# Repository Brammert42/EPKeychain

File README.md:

# DisplayKeychain
This repository is used to track FW development for Display Keychain using a RP2040 and waveshare Display.

# Manual
## Next image  
Holding the middle button for 4 seconds changes the image on the display to next image in the list.

## Previous image
Holding the middle button and the left button (button closet to the small hole) for 4 seconds changes the image on the display to previous image in the list.

## Uploading new FW  
Get the FW files here:   https://github.com/Brammert42/EPKeychain/tree/main/FW%20version
1: insert push pin in the hole next to the "previous" button untill you feel a "click"  
2: while the push pin is inserted insert the micro USB.  
3: on your PC the keychain will show up as flash drive as RPI-RP2, drag the new FW file into this

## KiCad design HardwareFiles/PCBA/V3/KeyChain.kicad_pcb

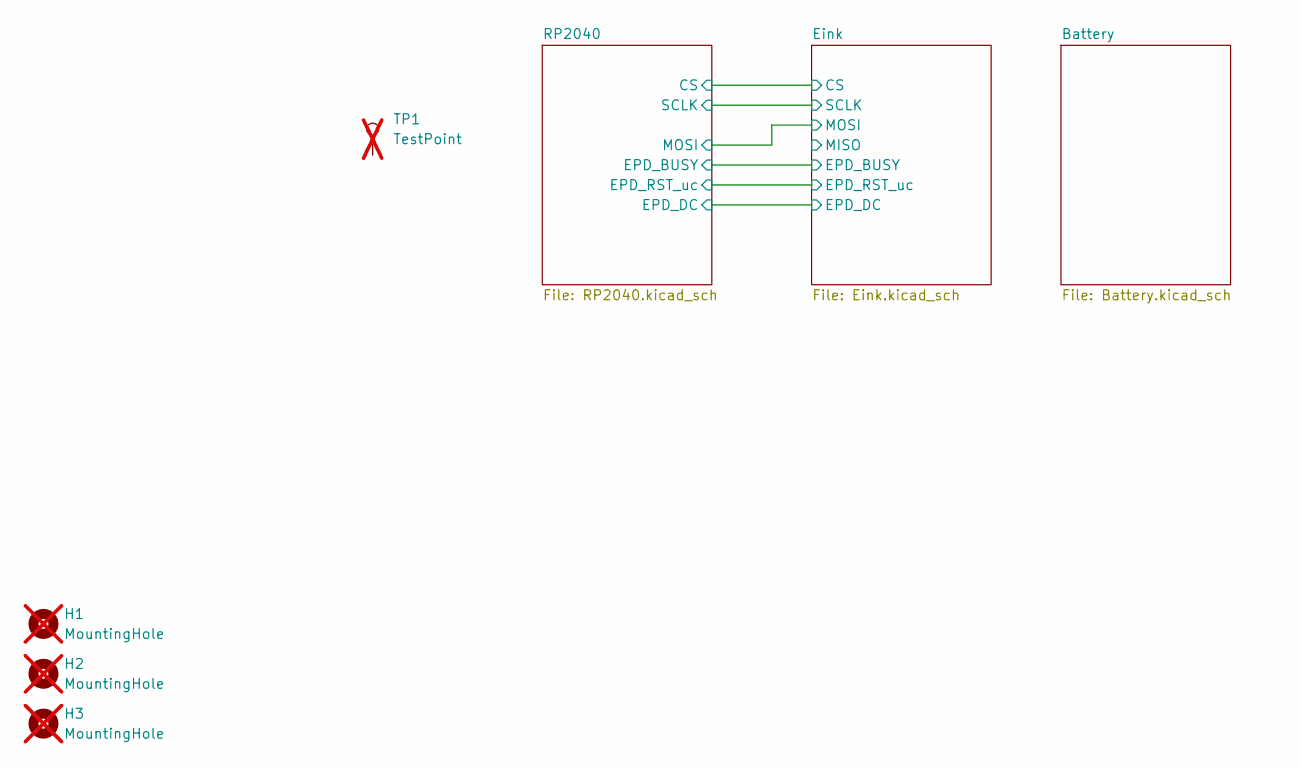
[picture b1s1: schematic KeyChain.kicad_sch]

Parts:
H1, H2, H3: MountingHole; MountingHole_2.1mm; not fitted
TP1: TestPoint; display; MPN dnf; not fitted

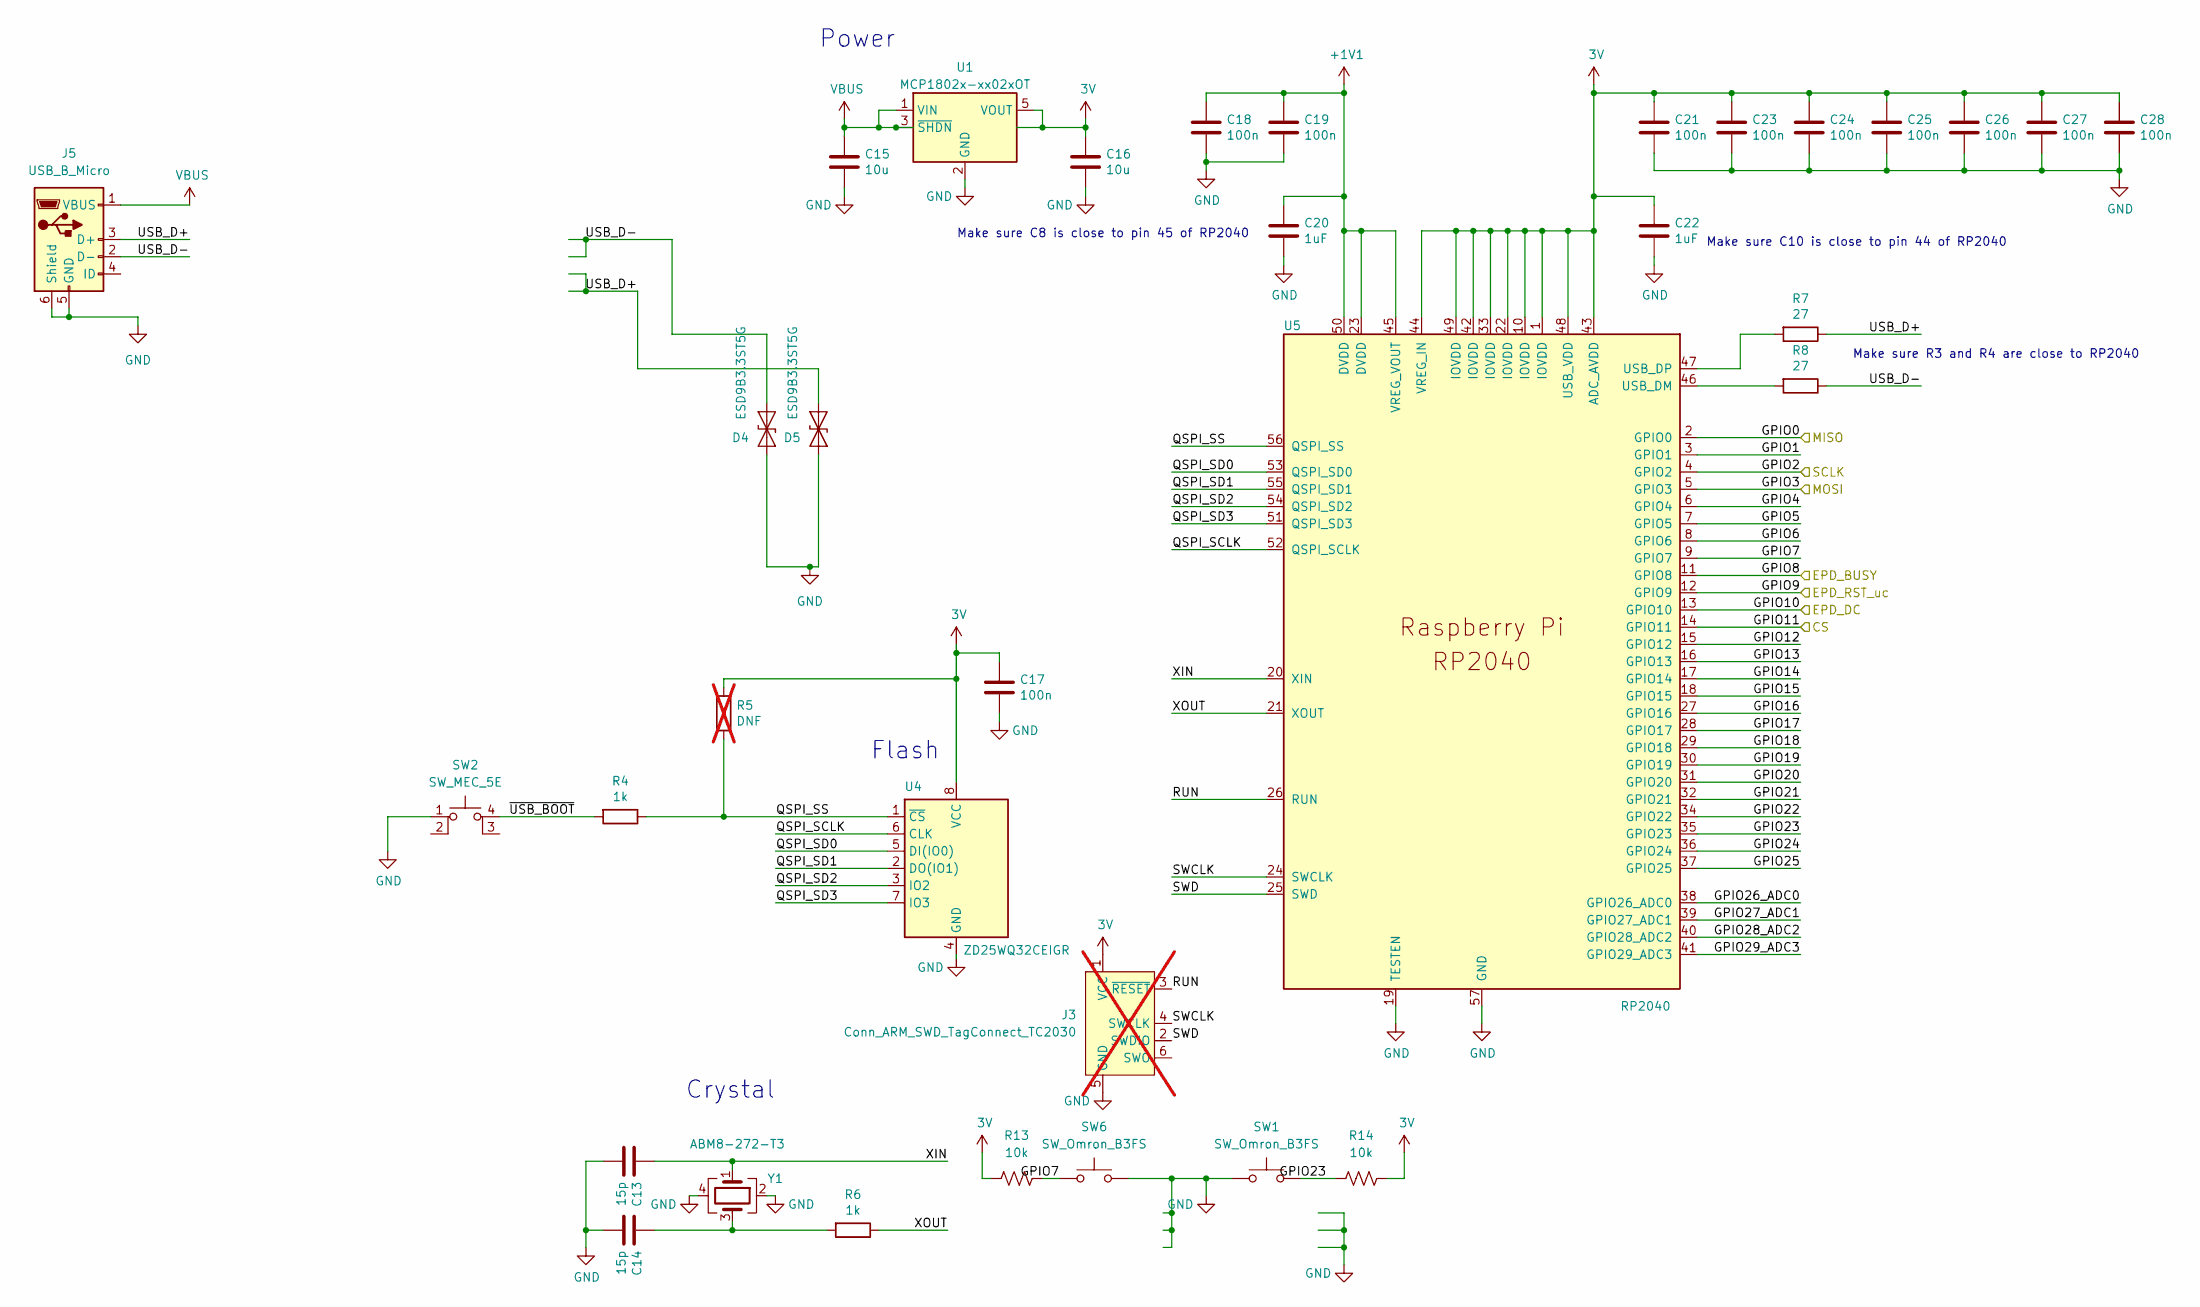
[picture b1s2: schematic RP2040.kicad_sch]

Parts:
C13, C14: 15p; C_0402_1005Metric; MPN C1548
C15, C16: 10u; C_0402_1005Metric; MPN C23733
C17, C18, C19, C21, C23, C24, C25, C26, C27, C28: 100n; C_0402_1005Metric; MPN C307331
C20, C22: 1uF; C_0402_1005Metric; MPN C52923
D4, D5: ESD9B3.3ST5G; D_SOD-923; MPN C3021104
J3: Conn_ARM_SWD_TagConnect_TC2030; Tag-Connect_TC2030-IDC-NL_2x03_P1.27mm_Vertical; not fitted
J5: USB_B_Micro; USB_Micro-B_Wuerth_614105150721_Vertical; MPN C668588
R4, R6: 1k; R_0402_1005Metric; MPN C11702
R5: DNF; R_0402_1005Metric; MPN dnf; not fitted
R7, R8: 27; R_0402_1005Metric; MPN C25100
R13, R14: 10k; R_0402_1005Metric; MPN C25744
SW1, SW6: SW_Omron_B3FS; SW_SPST_Omron_B3FS-100xP; MPN C5127964
SW2: SW_MEC_5E; SW_SPST_TL3342; MPN C318884
U1: MCP1802x-xx02xOT; SOT-23-5; MPN C7419952
U4: ZD25WQ32CEIGR; SON50P300X200X60-9N; MPN C5258281
U5: RP2040; QFN-56-1EP_7x7mm_P0.4mm_EP3.2x3.2mm; MPN C2040
Y1: ABM8-272-T3; Crystal_SMD_3225-4Pin_3.2x2.5mm; MPN C9002

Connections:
3V: C16.1, C17.1, C21.1, C22.1, C23.1, C24.1, C25.1, C26.1, C27.1, C28.1, J3.1 (VCC), R5.1, R13.1, R14.2, U1.4 (NC), U1.5 (VOUT), U4.8 (VCC), U5.1 (IOVDD), U5.10 (IOVDD), U5.22 (IOVDD), U5.33 (IOVDD), U5.42 (IOVDD), U5.43 (ADC_AVDD), U5.44 (VREG_IN), U5.48 (USB_VDD), U5.49 (IOVDD); also elsewhere on the board
+1V1: C18.1, C19.1, C20.1, U5.23 (DVDD), U5.45 (VREG_VOUT), U5.50 (DVDD)
/Eink/CLK: U5.4 (GPIO2); also elsewhere on the board
/Eink/DIN: U5.5 (GPIO3); also elsewhere on the board
/Eink/EPD_BUSY: U5.11 (GPIO8); also elsewhere on the board
/Eink/EPD_CS: U5.14 (GPIO11); also elsewhere on the board
/Eink/EPD_DC: U5.13 (GPIO10); also elsewhere on the board
/Eink/EPD_RST: U5.12 (GPIO9); also elsewhere on the board
/RP2040/GPIO0: U5.2 (GPIO0)
/RP2040/GPIO1: U5.3 (GPIO1)
/RP2040/GPIO4: U5.6 (GPIO4)
/RP2040/GPIO5: U5.7 (GPIO5)
/RP2040/GPIO6: U5.8 (GPIO6)
/RP2040/GPIO7: R13.2, SW6.1, U5.9 (GPIO7)
/RP2040/GPIO12: U5.15 (GPIO12)
/RP2040/GPIO13: U5.16 (GPIO13)
/RP2040/GPIO14: U5.17 (GPIO14)
/RP2040/GPIO15: U5.18 (GPIO15)
/RP2040/GPIO16: U5.27 (GPIO16)
/RP2040/GPIO17: U5.28 (GPIO17)
/RP2040/GPIO18: U5.29 (GPIO18)
/RP2040/GPIO19: U5.30 (GPIO19)
/RP2040/GPIO20: U5.31 (GPIO20)
/RP2040/GPIO21: U5.32 (GPIO21)
/RP2040/GPIO22: U5.34 (GPIO22)
/RP2040/GPIO23: R14.1, SW1.2, U5.35 (GPIO23)
/RP2040/GPIO24: U5.36 (GPIO24)
/RP2040/GPIO25: U5.37 (GPIO25)
/RP2040/GPIO26_ADC0: U5.38 (GPIO26_ADC0)
/RP2040/GPIO27_ADC1: U5.39 (GPIO27_ADC1)
/RP2040/GPIO28_ADC2: U5.40 (GPIO28_ADC2)
/RP2040/GPIO29_ADC3: U5.41 (GPIO29_ADC3)
/RP2040/QSPI_SCLK: U4.6 (CLK), U5.52 (QSPI_SCLK)
/RP2040/QSPI_SD0: U4.5 (DI(IO0)), U5.53 (QSPI_SD0)
/RP2040/QSPI_SD1: U4.2 (DO(IO1)), U5.55 (QSPI_SD1)
/RP2040/QSPI_SD2: U4.3 (IO2), U5.54 (QSPI_SD2)
/RP2040/QSPI_SD3: U4.7 (IO3), U5.51 (QSPI_SD3)
/RP2040/QSPI_SS: R4.1, R5.2, U4.1 (~CS), U5.56 (QSPI_SS)
/RP2040/RUN: J3.3 (~RESET), U5.26 (RUN)
/RP2040/SWCLK: J3.4 (SWCLK), U5.24 (SWCLK)
/RP2040/SWD: J3.2 (SWDIO), U5.25 (SWD)
/RP2040/USB_D+: D5.1 (A1), J5.3 (D+), R7.1
/RP2040/USB_D-: D4.1 (A1), J5.2 (D-), R8.1
/RP2040/XIN: C13.1, U5.20 (XIN), Y1.1
/RP2040/XOUT: R6.1, U5.21 (XOUT)
/RP2040/~USB_BOOT: R4.2, SW2.4 (A)
GND: C13.2, C14.2, C15.2, C16.2, C17.2, C18.2, C19.2, C20.2, C21.2, C22.2, C23.2, C24.2, C25.2, C26.2, C27.2, C28.2, D4.2 (A2), D5.2 (A2), J3.5 (GND), J5.5 (GND), J5.6 (Shield), SW1.1, SW2.1, SW6.2, U1.2 (GND), U4.4 (GND), U5.19 (TESTEN), U5.57 (GND), Y1.2, Y1.4; also elsewhere on the board
unnamed: C14.1, R6.2, Y1.3
unnamed: R8.2, U5.46 (USB_DM)
unnamed: R7.2, U5.47 (USB_DP)
VBUS: C15.1, J5.1 (VBUS), U1.1 (VIN), U1.3 (~SHDN)

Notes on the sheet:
Make sure R3 and R4 are close to RP2040
Power
Crystal
Make sure C10 is close to pin 44 of RP2040
Flash
Make sure C8 is close to pin 45 of RP2040

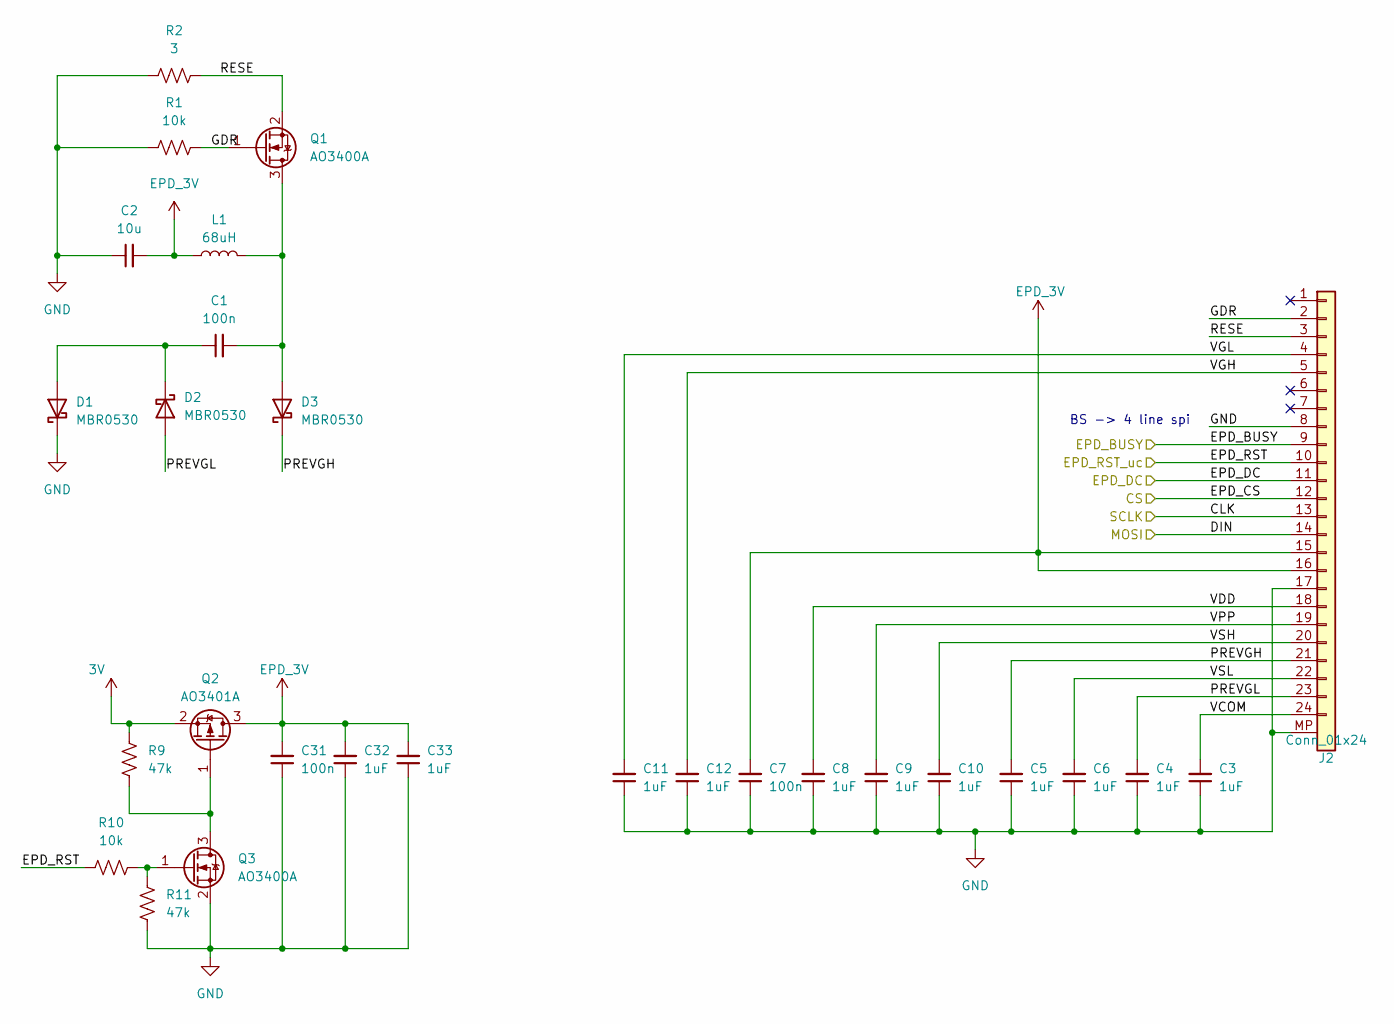
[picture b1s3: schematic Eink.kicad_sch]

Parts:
C1, C7, C31: 100n; C_0402_1005Metric; MPN C307331
C2: 10u; C_0402_1005Metric; MPN C23733
C3, C4, C5, C6, C8, C9, C10, C11, C12, C32, C33: 1uF; C_0402_1005Metric; MPN C52923
D1, D2, D3: MBR0530; D_SOD-123; MPN C8598
J2: Conn_01x24; Hirose_FH12-24S-0.5SH_1x24-1MP_P0.50mm_Horizontal; MPN C262669
L1: 68uH; L_1210_3225Metric; MPN C295164
Q1, Q3: AO3400A; SOT-23; MPN C20917
Q2: AO3401A; SOT-23; MPN C15127
R1, R10: 10k; R_0402_1005Metric; MPN C25744
R2: 3; R_0402_1005Metric; MPN C321178
R9, R11: 47k; R_0402_1005Metric; MPN C25792

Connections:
3V: Q2.2 (S), R9.2; also elsewhere on the board
/Eink/CLK: J2.13; also elsewhere on the board
/Eink/DIN: J2.14; also elsewhere on the board
/Eink/EPD_BUSY: J2.9; also elsewhere on the board
/Eink/EPD_CS: J2.12; also elsewhere on the board
/Eink/EPD_DC: J2.11; also elsewhere on the board
/Eink/EPD_RST: J2.10, R10.2; also elsewhere on the board
/Eink/GDR: J2.2, Q1.1 (G), R1.2
/Eink/PREVGH: C5.2, D3.1 (K), J2.21
/Eink/PREVGL: C4.2, D2.2 (A), J2.23
/Eink/RESE: J2.3, Q1.2 (S), R2.2
/Eink/VCOM: C3.2, J2.24
/Eink/VDD: C8.2, J2.18
/Eink/VGH: C12.2, J2.5
/Eink/VGL: C11.2, J2.4
/Eink/VPP: C9.2, J2.19
/Eink/VSH: C10.2, J2.20
/Eink/VSL: C6.2, J2.22
EPD_3V: C2.2, C7.2, C31.2, C32.2, C33.2, J2.15, J2.16, L1.1, Q2.3 (D)
GND: C2.1, C3.1, C4.1, C5.1, C6.1, C7.1, C8.1, C9.1, C10.1, C11.1, C12.1, C31.1, C32.1, C33.1, D1.1 (K), J2.8, J2.17, J2.MP, Q3.2 (S), R1.1, R2.1, R11.1; also elsewhere on the board
unnamed: C1.1, D1.2 (A), D2.1 (K)
unnamed: C1.2, D3.2 (A), L1.2, Q1.3 (D)
unnamed: Q2.1 (G), Q3.3 (D), R9.1
unnamed: Q3.1 (G), R10.1, R11.2

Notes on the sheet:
BS -> 4 line spi

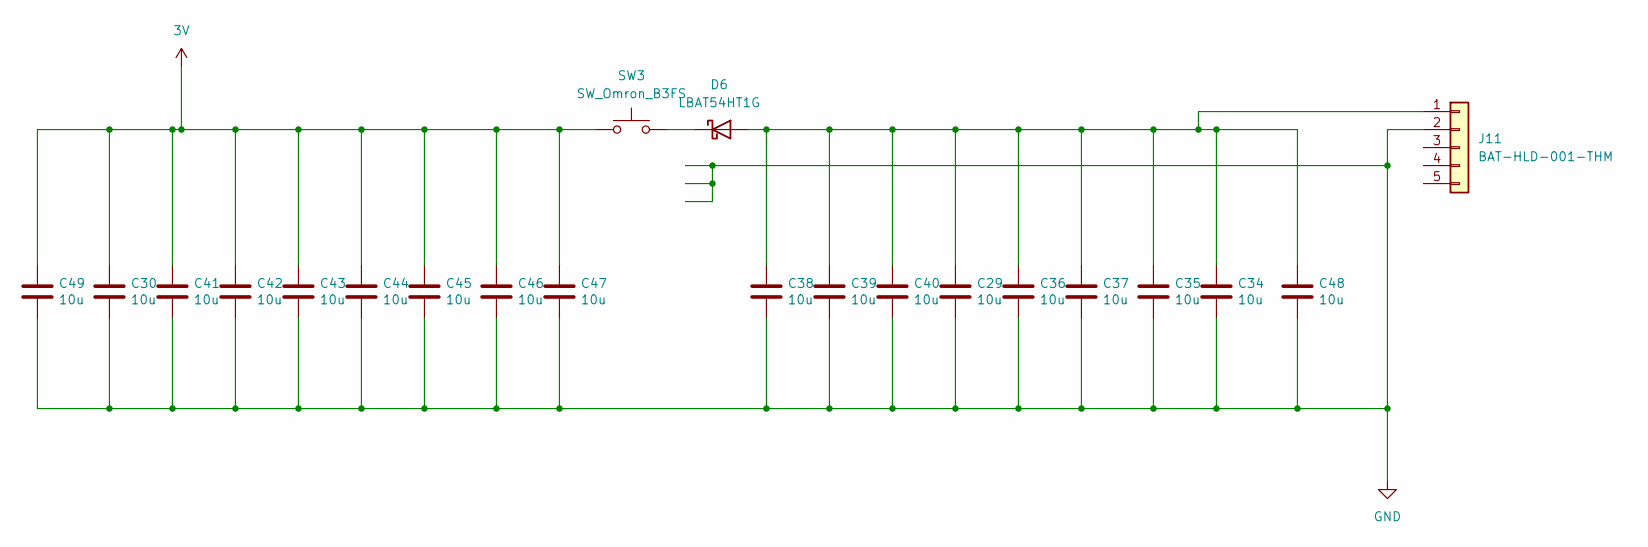
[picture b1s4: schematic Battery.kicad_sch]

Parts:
C29, C30, C34, C35, C36, C37, C38, C39, C40, C41, C42, C43, C44, C45, C46, C47, C48, C49: 10u; C_0402_1005Metric; MPN C23733
D6: LBAT54HT1G; D_SOD-323; MPN C12744
J11: BAT-HLD-001-THM; BatteryHolder_Multicomp_BC-2001_1x2032; MPN C2979177
SW3: SW_Omron_B3FS; SW_SPST_Omron_B3FS-100xP; MPN C5127964

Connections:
3V: C30.1, C41.1, C42.1, C43.1, C44.1, C45.1, C46.1, C47.1, C49.1, SW3.1; also elsewhere on the board
GND: C29.2, C30.2, C34.2, C35.2, C36.2, C37.2, C38.2, C39.2, C40.2, C41.2, C42.2, C43.2, C44.2, C45.2, C46.2, C47.2, C48.2, C49.2, J11.2; also elsewhere on the board
unnamed: C29.1, C34.1, C35.1, C36.1, C37.1, C38.1, C39.1, C40.1, C48.1, D6.2 (A), J11.1
unnamed: D6.1 (K), SW3.2

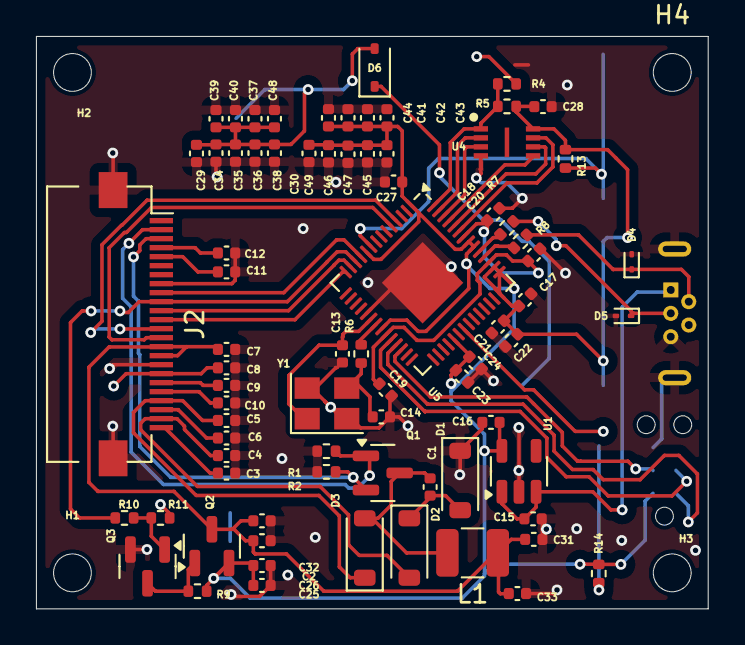
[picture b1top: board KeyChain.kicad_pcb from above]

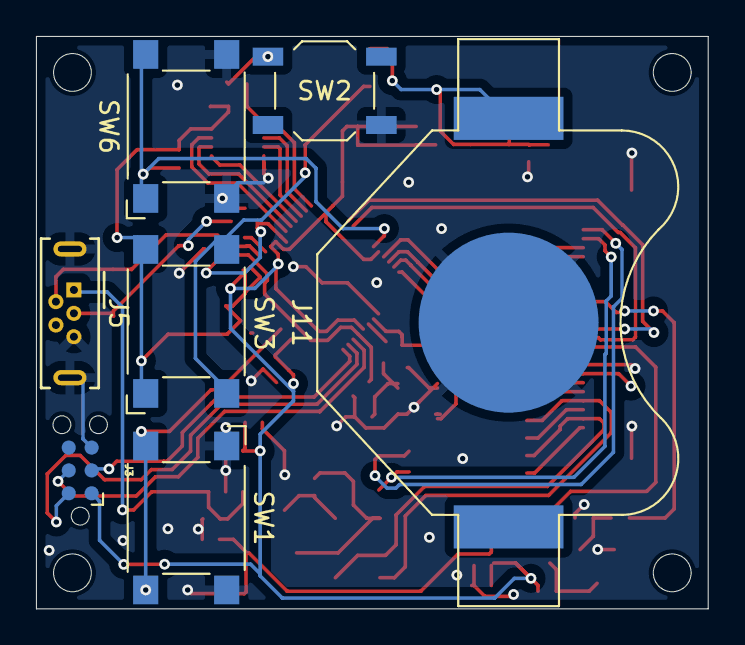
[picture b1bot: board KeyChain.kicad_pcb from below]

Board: 2 copper layers, 37.3 x 31.8 mm, 88 parts (7 on the bottom side), 47 nets.

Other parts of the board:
H4: MountingHole; MountingHole_2.1mm

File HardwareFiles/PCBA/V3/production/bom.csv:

Designator,Footprint,Quantity,Value,LCSC Part #
"C1, C17, C18, C19, C21, C23, C24, C25, C26, C27, C28, C31, C7",0402,13,100n,C307331
"C10, C11, C12, C20, C22, C3, C32, C33, C4, C5, C6, C8, C9",0402,13,1uF, C52923
"C13, C14",0402,2,15p,C1548
"C15, C16, C2, C29, C30, C34, C35, C36, C37, C38, C39, C40, C41, C42, C43, C44, C45, C46, C47, C48, C49",0402,21,10u,C23733
"D1, D2, D3",D_SOD-123,3,MBR0530, C8598
"D4, D5",D_SOD-923,2,ESD9B3.3ST5G,C3021104
D6,D_SOD-323,1,LBAT54HT1G,C12744
J11,BatteryHolder_Multicomp_BC-2001_1x2032,1,BAT-HLD-001-THM,C2979177
J2,Hirose_FH12-24S-0.5SH_1x24-1MP_P0.50mm_Horizontal,1,Conn_01x24,C262669
J5,USB_Micro-B_Wuerth_614105150721_Vertical,1,USB_B_Micro,C668588
L1,1210,1,68uH,C295164
"Q1, Q3",SOT-23,2,AO3400A,C20917
Q2,SOT-23,1,AO3401A,C15127
"R1, R10, R13, R14",0402,4,10k,C25744
"R11, R9",0402,2,47k, C25792
R2,0402,1,3,C321178
"R4, R6",0402,2,1k,C11702
R5,0402,1,DNF,dnf
"R7, R8",0402,2,27,C25100
"SW1, SW3, SW6",SW_SPST_Omron_B3FS-100xP,3,SW_Omron_B3FS,C5127964
SW2,SW_SPST_TL3342,1,SW_MEC_5E,C318884
TP1,display,1,TestPoint,dnf
U1,SOT-23-5,1,MCP1802x-xx02xOT, C7419952
U4,SON50P300X200X60-9N,1,ZD25WQ32CEIGR,C5258281
U5,QFN-56-1EP_7x7mm_P0.4mm_EP3.2x3.2mm,1,RP2040,C2040
Y1,Crystal_SMD_3225-4Pin_3.2x2.5mm,1,ABM8-272-T3, C9002

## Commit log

2024-07-25 Update README.md
    first draft
2024-07-25 Update README.md
    added link and images
2026-03-31 added folder codeforai
    added folder
2026-03-31 Add local qrcodegen compatibility implementation
